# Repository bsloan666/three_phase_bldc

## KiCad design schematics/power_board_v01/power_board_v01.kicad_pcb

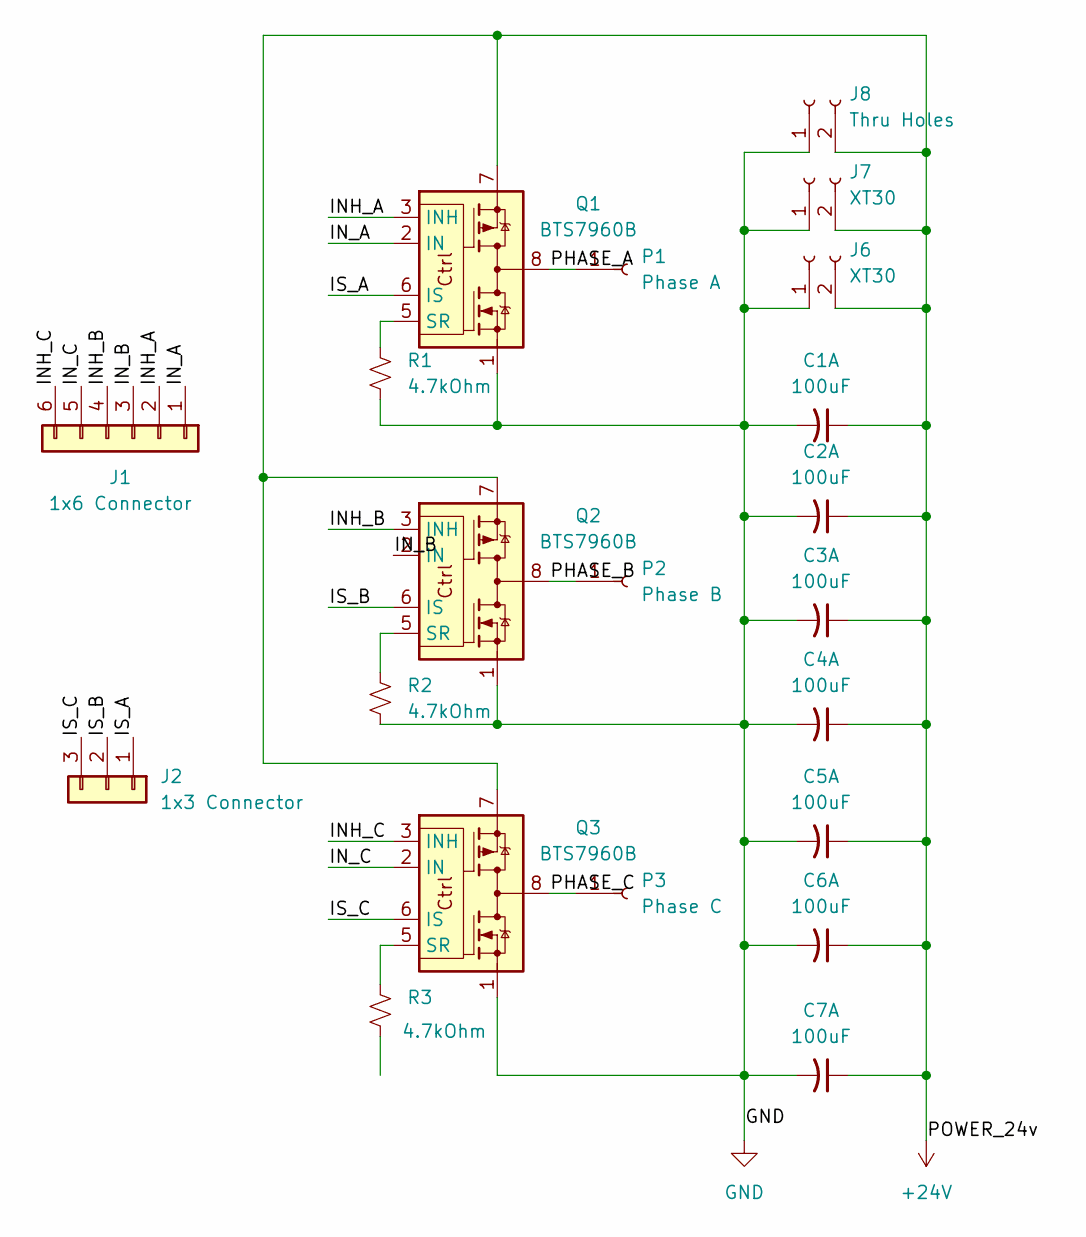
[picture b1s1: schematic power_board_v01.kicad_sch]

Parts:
C1, C2, C3, C4, C5, C6, C7: 100uF
J1: 1x6 Connector
J2: 1x3 Connector
J6, J7: XT30
J8: Thru Holes
P1: Phase A
P2: Phase B
P3: Phase C
Q1, Q2, Q3: BTS7960B; TO-263-7_TabPin8
R1, R2, R3: 4.7kOhm

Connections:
+24V: C1.1, C2.1, C3.1, C4.1, C5.1, C6.1, C7.1, J6.2, J7.2, J8.2, Q1.7, Q2.7, Q3.7
/INH_A: J1.2, Q1.3 (INH)
/INH_B: J1.4, Q2.3 (INH)
/INH_C: J1.6, Q3.3 (INH)
/IN_A: J1.1, Q1.2 (IN)
/IN_B: J1.3, Q2.2 (IN)
/IN_C: J1.5, Q3.2 (IN)
/IS_A: J2.1, Q1.6 (IS)
/IS_B: J2.2, Q2.6 (IS)
/IS_C: J2.3, Q3.6 (IS)
/PHASE_A: P1.1, Q1.4, Q1.8
/PHASE_B: P2.1, Q2.4, Q2.8
/PHASE_C: P3.1, Q3.4, Q3.8
GND: C1.2, C2.2, C3.2, C4.2, C5.2, C6.2, C7.2, J6.1, J7.1, J8.1, Q1.1, Q2.1, Q3.1, R1.2, R2.2, R3.2
unnamed: Q1.5 (SR), R1.1
unnamed: Q2.5 (SR), R2.1
unnamed: Q3.5 (SR), R3.1

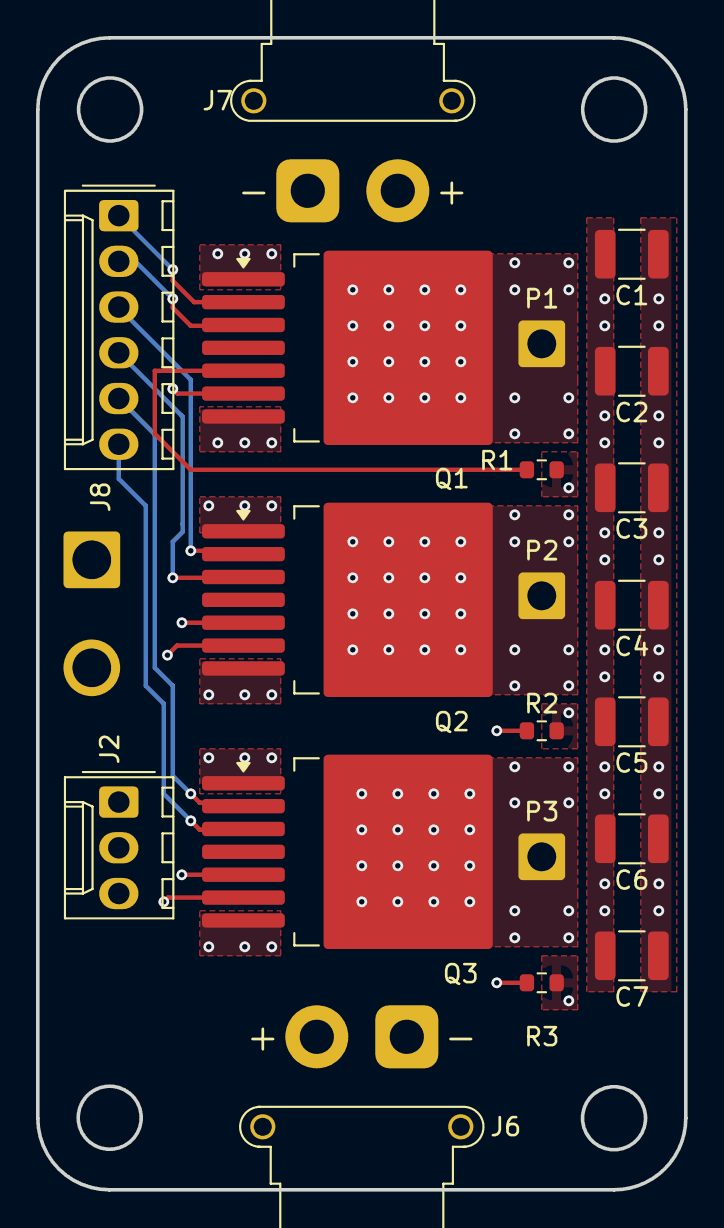
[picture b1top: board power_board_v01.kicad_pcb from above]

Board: 4 copper layers, 36.0 x 64.0 mm, 21 parts (0 on the bottom side), 17 nets.

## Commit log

2026-04-14 initial checkin
2026-04-24 more documentation from Mr. Gemini
2026-05-31 added trapezoidal using interrupts
2026-06-14 initial checking of 3-phase ADRC algorithm
2026-06-15 added FOC stuff for homemade driver and ADRC for Ransanx driver.
2026-06-20 added CANbus examples
2026-06-21 added temp sensor example
2026-06-21 removed extra CANbus examples
